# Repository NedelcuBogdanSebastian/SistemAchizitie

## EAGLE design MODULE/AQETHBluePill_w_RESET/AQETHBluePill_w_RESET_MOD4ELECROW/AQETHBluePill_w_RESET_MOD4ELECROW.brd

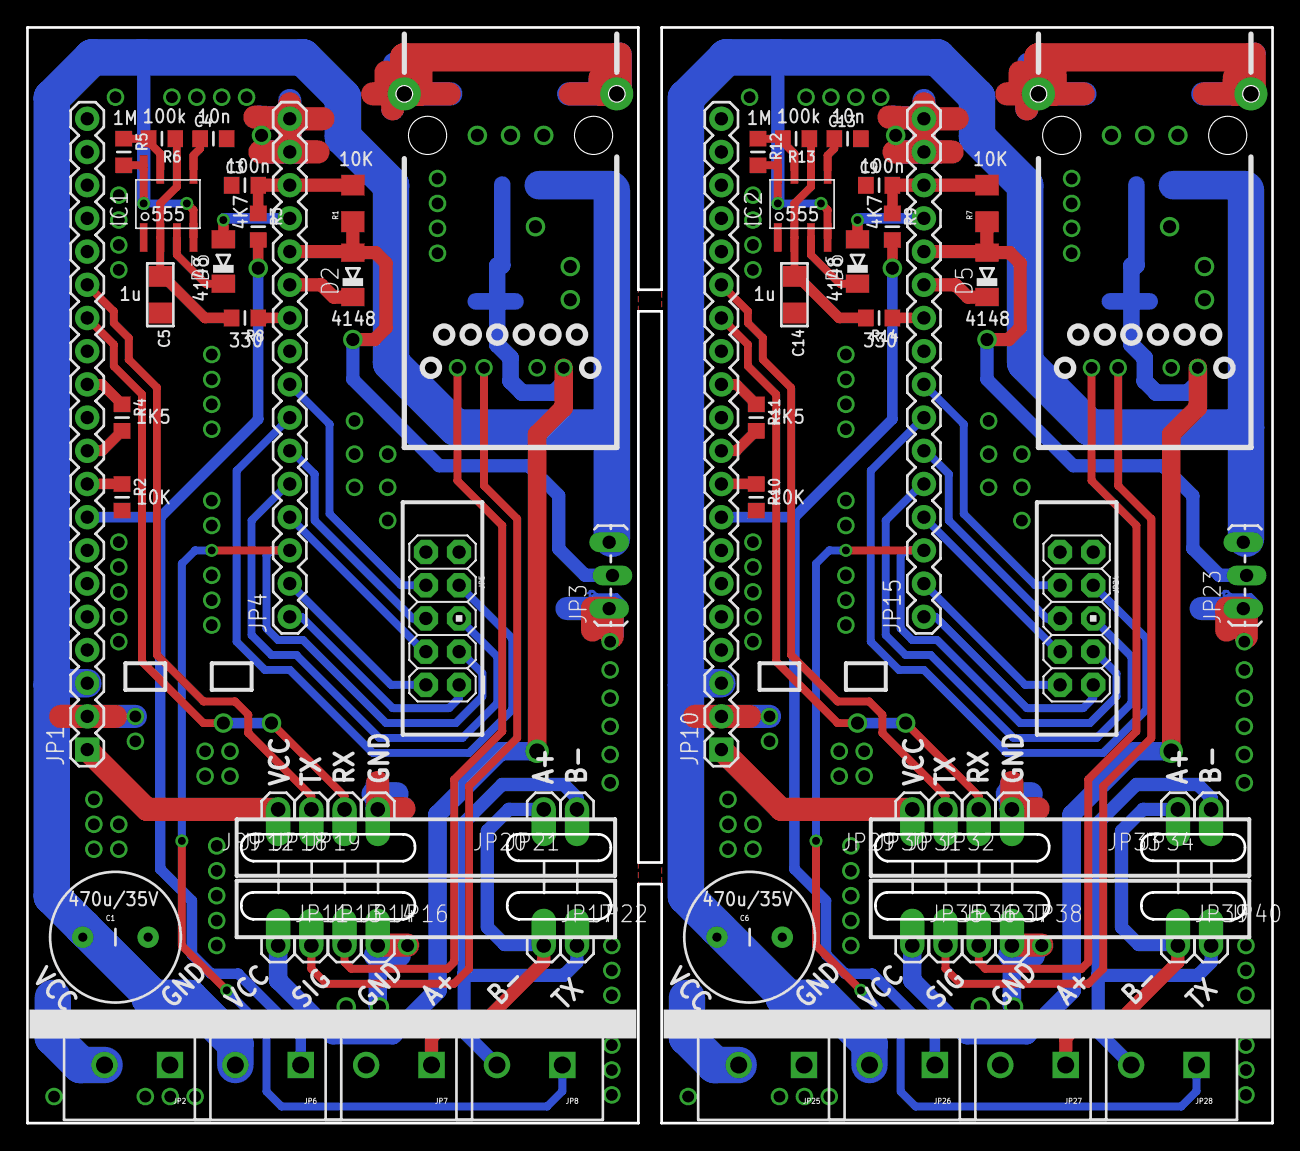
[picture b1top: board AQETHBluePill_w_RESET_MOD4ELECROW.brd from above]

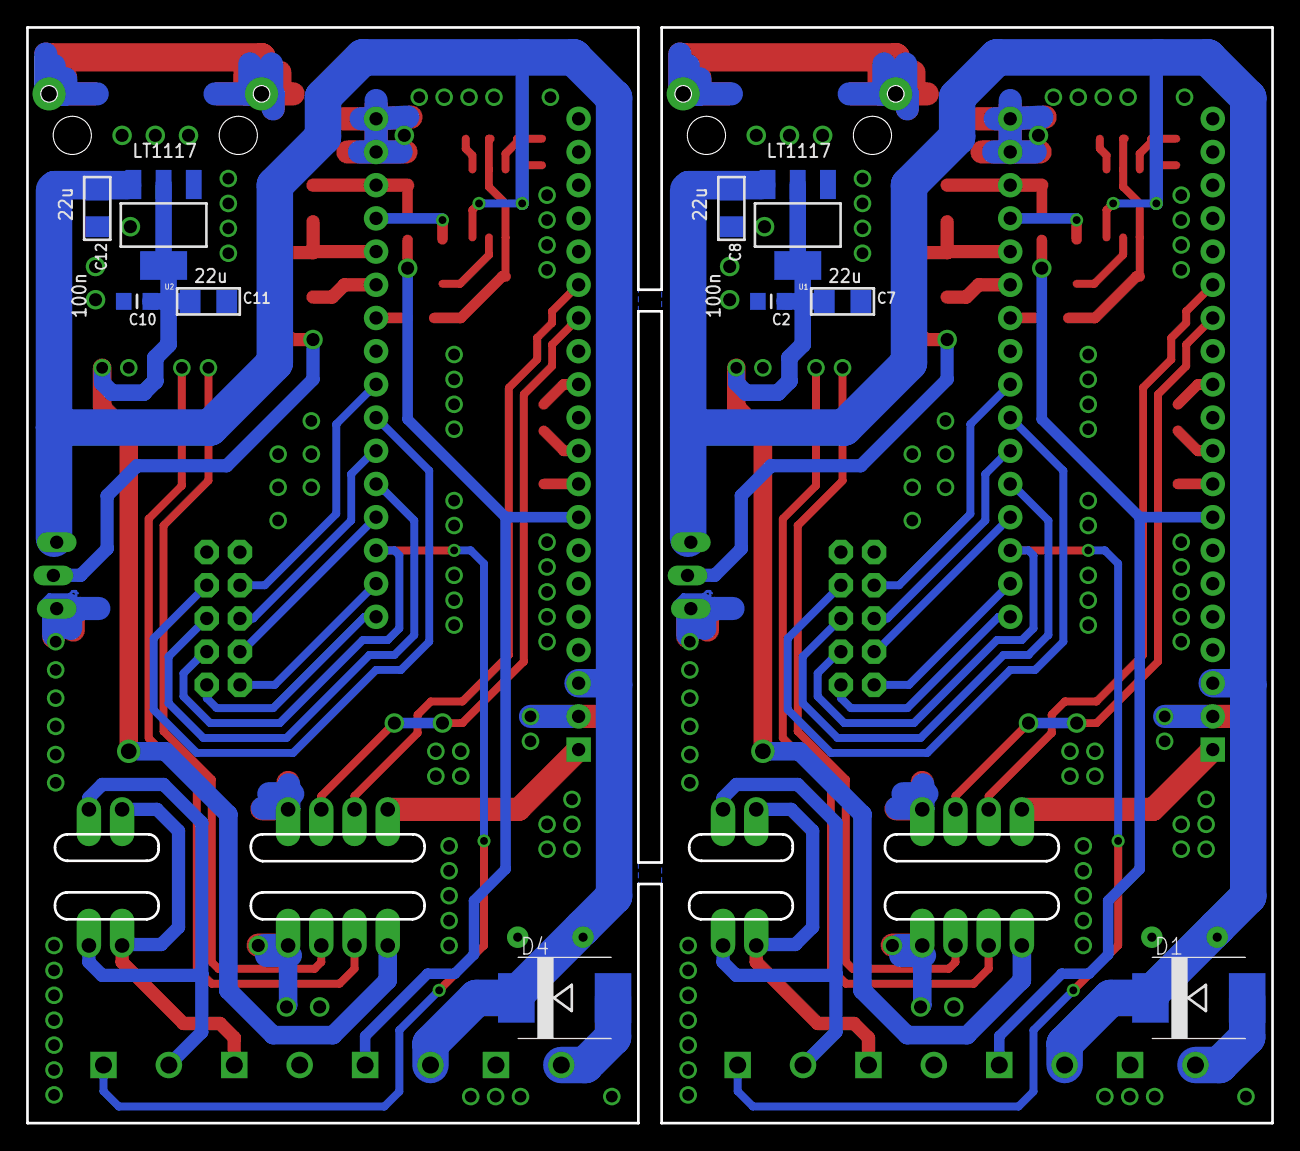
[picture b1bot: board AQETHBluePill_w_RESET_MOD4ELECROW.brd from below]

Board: 2 copper layers, 95.2 x 83.8 mm, 78 parts (10 on the bottom side), 60 nets.

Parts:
C1, C6: 470uF/35V; CAP-PTH-5MM
C2, C3, C9, C10: 100n; _0805MP
C4, C13: 10n; _0805MP
C5, C14: 1u; 1206
C7, C8, C11, C12: 22u; 1206
D1, D4: SS34; SMC
D2, D3, D5, D6: 1N4148; MINIMELF
IC1, IC2: IC_555-SOIC8; SOIC-8
JP1, JP10: M20; 1X20
JP2, JP6, JP7, JP8, JP25, JP26, JP27, JP28: SCREWTERMINAL-5MM-2
JP3, JP23: 1X03_LOCK_LONGPADS
JP4, JP15: M16PTH; 1X16
JP5, JP24: M05X2PTH; AVR_ICSP
JP9, JP11, JP12, JP13, JP14, JP16, JP17, JP18, JP19, JP20, JP21, JP22, JP29, JP30, JP31, JP32, JP33, JP34, JP35, JP36, JP37, JP38, JP39, JP40: M01OFFSET; 1X01_OFFSET
R1, R7: 10K; 1206
R2, R10: 10K; _0805MP
R3, R9: 4k7; _0805MP
R4, R11: 1K5; _0805MP
R5, R12: 1M; _0805MP
R6, R13: 100K; _0805MP
R8, R14: 330; _0805MP
U1, U2: SOT223

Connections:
3.3V: C3.2, JP4.14, R1.2, R3.1
3.3V1: C9.2, JP15.14, R7.2, R9.1
3V3_SECOND: JP1.1, JP9.1
3V3_SECOND1: JP10.1, JP29.1
5V: C1.1, C8.1, D1.C, IC1.4, IC1.8, JP1.3, JP3.3, JP6.2, R5.2, U1.3
5V1: C6.1, C12.1, D4.C, IC2.4, IC2.8, JP10.3, JP23.3, JP26.2, R12.2, U2.3
+A_1: JP27.1, JP33.1, JP39.1
+A_485: JP7.1, JP17.1, JP20.1
-B_1: JP28.2, JP34.1, JP40.1
-B_485: JP8.2, JP21.1, JP22.1
CTRL: C4.1, IC1.5
CTRL1: C13.1, IC2.5
DS18S20_SIGNAL_PIN: JP1.8, JP6.1, R3.2
DS18S20_SIGNAL_PIN1: JP10.8, JP26.1, R9.2
GND: C1.2, C2.2, C3.1, C4.2, C5.2, C7.2, C8.2, IC1.1, JP1.2, JP2.1, JP3.1, JP4.15, JP4.16, JP5.9, JP5.10, JP7.2, JP16.1, JP19.1, R2.2, U1.1
GND2: C6.2, C9.1, C10.2, C11.2, C12.2, C13.2, C14.2, IC2.1, JP10.2, JP15.15, JP15.16, JP23.1, JP24.9, JP24.10, JP25.1, JP27.2, JP32.1, JP38.1, R10.2, U2.1
HEARTBEAT: JP4.10, R8.1
HEARTBEAT1: JP15.10, R14.1
K1: JP4.1, JP5.1
K2: JP4.2, JP5.2
K3: JP15.1, JP24.1
K3_OR_TX1: JP15.3, JP24.3, JP28.1
K3_OR_TX2: JP4.3, JP5.3, JP8.1
K4: JP4.4, JP5.4
K5: JP4.5, JP5.5
K6: JP4.6, JP5.6
K7: JP4.7, JP5.7
K8: JP4.8, JP5.8
K9: JP15.2, JP24.2
K10: JP15.4, JP24.4
K11: JP15.5, JP24.5
K12: JP15.6, JP24.6
K13: JP15.7, JP24.7
K14: JP15.8, JP24.8
unnamed: JP1.10, R4.2
unnamed: JP1.9, R2.1
unnamed: JP1.12, R4.1
unnamed: JP10.9, R10.1
unnamed: D4.A, JP25.2
unnamed: C5.1, IC1.2, IC1.6, R6.1, R8.2
unnamed: D3.C, IC1.3
unnamed: IC1.7, R5.1, R6.2
unnamed: JP10.10, R11.2
unnamed: JP10.12, R11.1
unnamed: C14.1, IC2.2, IC2.6, R13.1, R14.2
unnamed: D1.A, JP2.2
unnamed: D6.C, IC2.3
unnamed: IC2.7, R12.1, R13.2
PB10_TX1: D5.C, JP15.11
PB10_TX3: D2.C, JP4.11
PB11_RX1: D5.A, JP15.12, JP23.2, R7.1
PB11_RX3: D2.A, JP3.2, JP4.12, R1.1
RESET: D3.A, JP4.13
RESET1: D6.A, JP15.13
RX1: JP1.14, JP18.1
RX2: JP10.14, JP31.1
TX1: JP1.15, JP12.1
TX2: JP10.15, JP30.1
VCC: C2.1, C7.1, JP11.1, U1.2, U1.4
VCC1: C10.1, C11.1, JP35.1, U2.2, U2.4

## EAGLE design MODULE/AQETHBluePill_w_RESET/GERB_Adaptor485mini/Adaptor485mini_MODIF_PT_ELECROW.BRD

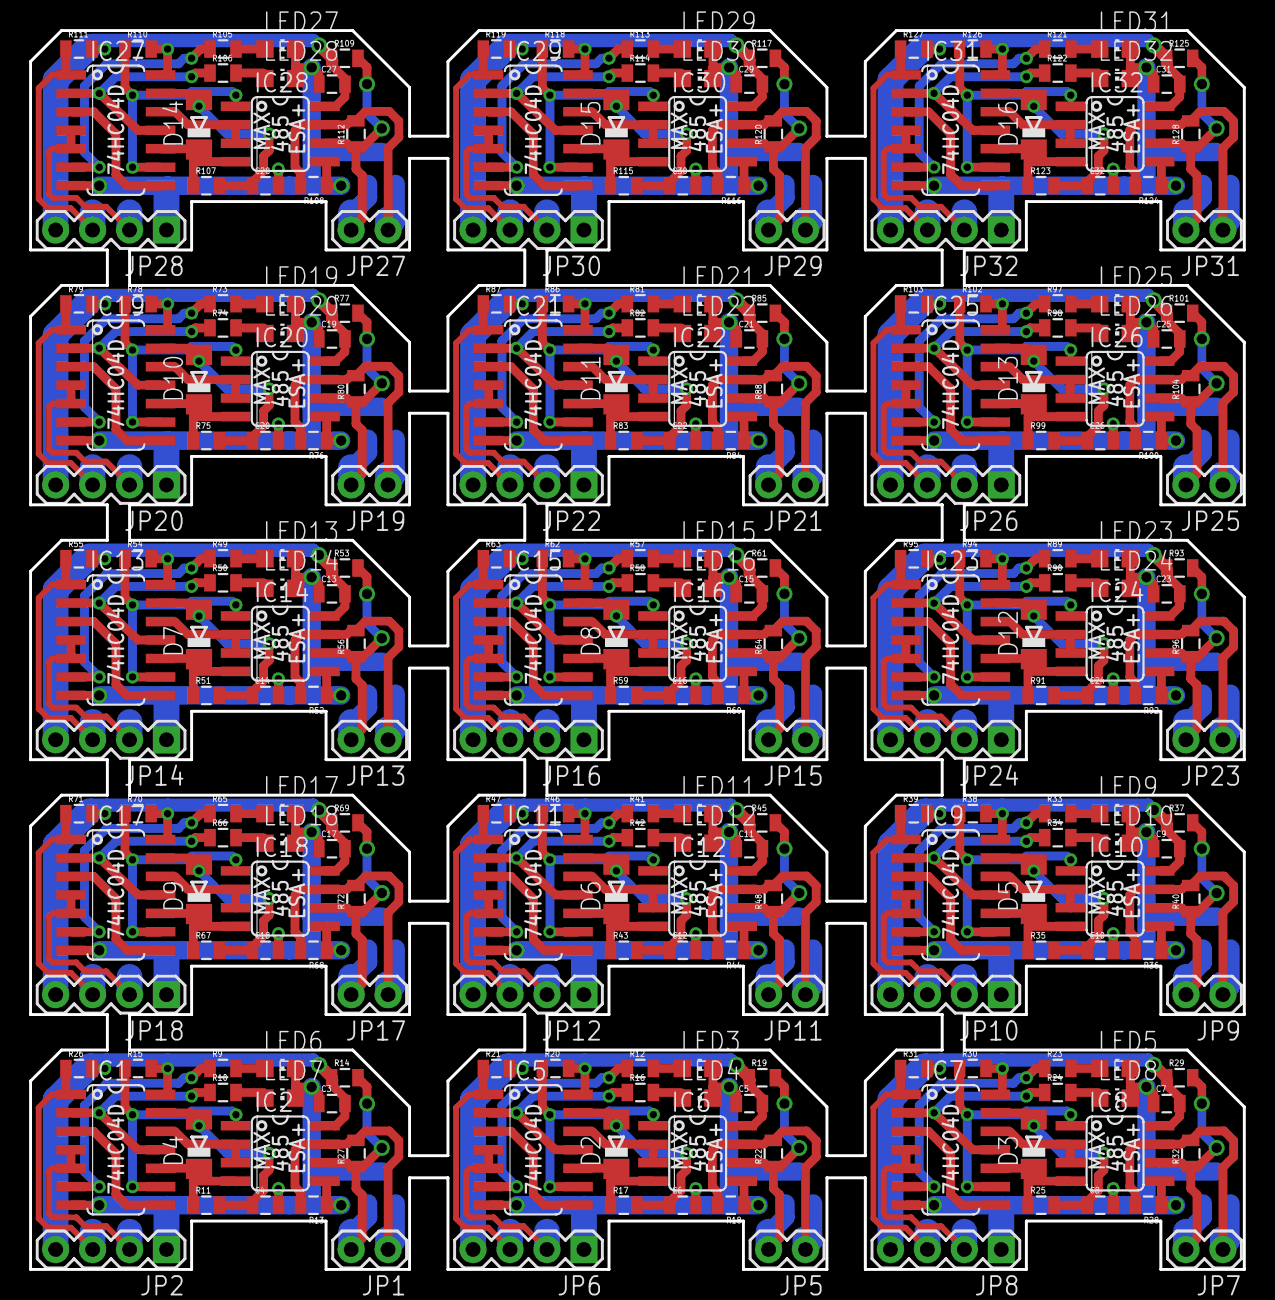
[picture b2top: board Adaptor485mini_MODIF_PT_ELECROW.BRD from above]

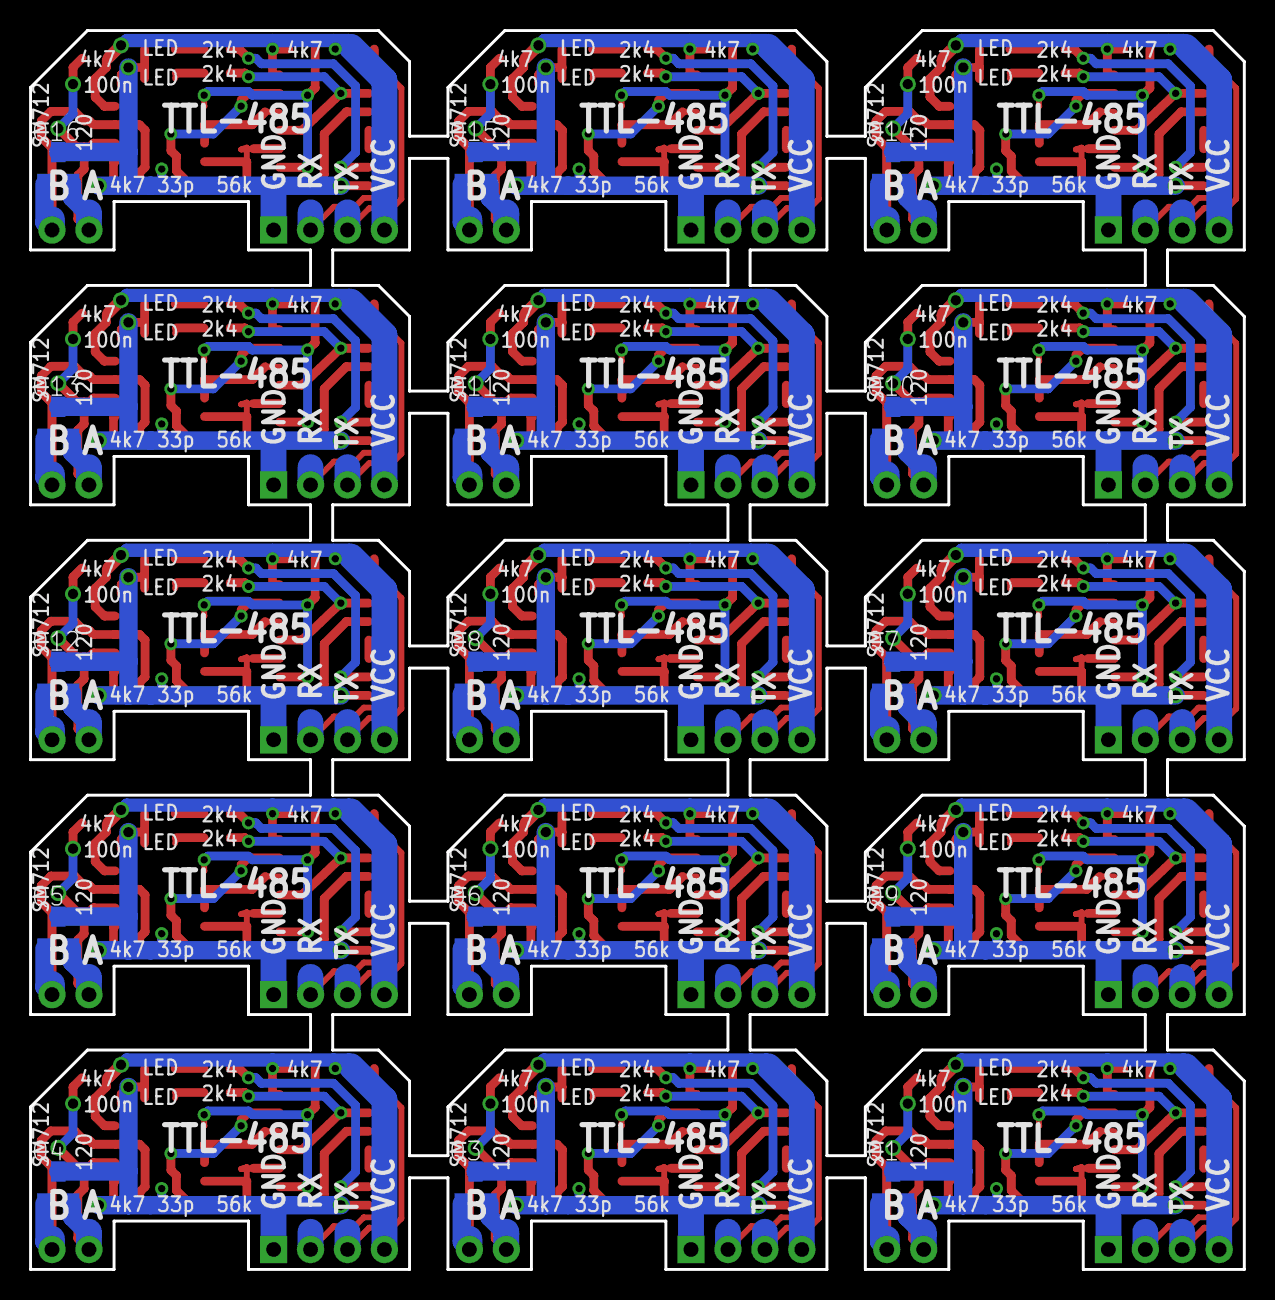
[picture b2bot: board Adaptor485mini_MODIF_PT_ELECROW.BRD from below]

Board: 2 copper layers, 83.5 x 85.2 mm, 270 parts (15 on the bottom side), 225 nets.

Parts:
C3, C5, C7, C9, C11, C13, C15, C17, C19, C21, C23, C25, C27, C29, C31: 100n; 0805
C4, C6, C8, C10, C12, C14, C16, C18, C20, C22, C24, C26, C28, C30, C32: 33pF; 0805
D2, D3, D4, D5, D6, D7, D8, D9, D10, D11, D12, D13, D14, D15, D16: 1N4148; MINIMELF
IC1, IC5, IC7, IC9, IC11, IC13, IC15, IC17, IC19, IC21, IC23, IC25, IC27, IC29, IC31: 74HC04D; SO14
IC2, IC6, IC8, IC10, IC12, IC14, IC16, IC18, IC20, IC22, IC24, IC26, IC28, IC30, IC32: MAX3468CSA; SO08
JP1, JP5, JP7, JP9, JP11, JP13, JP15, JP17, JP19, JP21, JP23, JP25, JP27, JP29, JP31: 1X02
JP2, JP6, JP8, JP10, JP12, JP14, JP16, JP18, JP20, JP22, JP24, JP26, JP28, JP30, JP32: 1X04
LED3, LED4, LED5, LED6, LED7, LED8, LED9, LED10, LED11, LED12, LED13, LED14, LED15, LED16, LED17, LED18, LED19, LED20, LED21, LED22, LED23, LED24, LED25, LED26, LED27, LED28, LED29, LED30, LED31, LED32: CHIP-LED0805
Q1, Q3, Q4, Q5, Q6, Q7, Q8, Q9, Q10, Q11, Q12, Q13, Q14, Q15, Q16: BCX70SMD; SOT23
R9, R10, R12, R16, R23, R24, R33, R34, R41, R42, R49, R50, R57, R58, R65, R66, R73, R74, R81, R82, R89, R90, R97, R98, R105, R106, R113, R114, R121, R122: 2K4; 0805
R11, R17, R25, R35, R43, R51, R59, R67, R75, R83, R91, R99, R107, R115, R123: 56K; 0805
R13, R14, R15, R18, R19, R20, R21, R26, R28, R29, R30, R31, R36, R37, R38, R39, R44, R45, R46, R47, R52, R53, R54, R55, R60, R61, R62, R63, R68, R69, R70, R71, R76, R77, R78, R79, R84, R85, R86, R87, R92, R93, R94, R95, R100, R101, R102, R103, R108, R109, R110, R111, R116, R117, R118, R119, R124, R125, R126, R127: 4K7; 0805
R22, R27, R32, R40, R48, R56, R64, R72, R80, R88, R96, R104, R112, R120, R128: 120; 0805

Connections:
3.3V: C3.2, IC1.14, IC2.8, JP2.4, R14.1, R15.2, R26.2
3.3V2: C5.2, IC5.14, IC6.8, JP6.4, R19.1, R20.2, R21.2
3.3V3: C7.2, IC7.14, IC8.8, JP8.4, R29.1, R30.2, R31.2
3.3V4: C9.2, IC9.14, IC10.8, JP10.4, R37.1, R38.2, R39.2
3.3V5: C11.2, IC11.14, IC12.8, JP12.4, R45.1, R46.2, R47.2
3.3V6: C13.2, IC13.14, IC14.8, JP14.4, R53.1, R54.2, R55.2
3.3V7: C15.2, IC15.14, IC16.8, JP16.4, R61.1, R62.2, R63.2
3.3V8: C17.2, IC17.14, IC18.8, JP18.4, R69.1, R70.2, R71.2
3.3V9: C19.2, IC19.14, IC20.8, JP20.4, R77.1, R78.2, R79.2
3.3V10: C21.2, IC21.14, IC22.8, JP22.4, R85.1, R86.2, R87.2
3.3V11: C23.2, IC23.14, IC24.8, JP24.4, R93.1, R94.2, R95.2
3.3V12: C25.2, IC25.14, IC26.8, JP26.4, R101.1, R102.2, R103.2
3.3V13: C27.2, IC27.14, IC28.8, JP28.4, R109.1, R110.2, R111.2
3.3V14: C29.2, IC29.14, IC30.8, JP30.4, R117.1, R118.2, R119.2
3.3V15: C31.2, IC31.14, IC32.8, JP32.4, R125.1, R126.2, R127.2
A+: IC2.6, JP1.2, Q1.2, R14.2, R27.1
A+2: IC6.6, JP5.2, Q3.2, R19.2, R22.1
A+3: IC8.6, JP7.2, Q4.2, R29.2, R32.1
A+4: IC10.6, JP9.2, Q5.2, R37.2, R40.1
A+5: IC12.6, JP11.2, Q6.2, R45.2, R48.1
A+6: IC14.6, JP13.2, Q7.2, R53.2, R56.1
A+7: IC16.6, JP15.2, Q8.2, R61.2, R64.1
A+8: IC18.6, JP17.2, Q9.2, R69.2, R72.1
A+9: IC20.6, JP19.2, Q10.2, R77.2, R80.1
A+10: IC22.6, JP21.2, Q11.2, R85.2, R88.1
A+11: IC24.6, JP23.2, Q12.2, R93.2, R96.1
A+12: IC26.6, JP25.2, Q13.2, R101.2, R104.1
A+13: IC28.6, JP27.2, Q14.2, R109.2, R112.1
A+14: IC30.6, JP29.2, Q15.2, R117.2, R120.1
A+15: IC32.6, JP31.2, Q16.2, R125.2, R128.1
B-: IC2.7, JP1.1, Q1.1, R13.2, R27.2
B-2: IC6.7, JP5.1, Q3.1, R18.2, R22.2
B-3: IC8.7, JP7.1, Q4.1, R28.2, R32.2
B-4: IC10.7, JP9.1, Q5.1, R36.2, R40.2
B-5: IC12.7, JP11.1, Q6.1, R44.2, R48.2
B-6: IC14.7, JP13.1, Q7.1, R52.2, R56.2
B-7: IC16.7, JP15.1, Q8.1, R60.2, R64.2
B-8: IC18.7, JP17.1, Q9.1, R68.2, R72.2
B-9: IC20.7, JP19.1, Q10.1, R76.2, R80.2
B-10: IC22.7, JP21.1, Q11.1, R84.2, R88.2
B-11: IC24.7, JP23.1, Q12.1, R92.2, R96.2
B-12: IC26.7, JP25.1, Q13.1, R100.2, R104.2
B-13: IC28.7, JP27.1, Q14.1, R108.2, R112.2
B-14: IC30.7, JP29.1, Q15.1, R116.2, R120.2
B-15: IC32.7, JP31.1, Q16.1, R124.2, R128.2
GND: C3.1, C4.2, IC1.7, IC2.5, JP2.1, LED6.C, LED7.C, Q1.3, R13.1
GND3: C5.1, C6.2, IC5.7, IC6.5, JP6.1, LED3.C, LED4.C, Q3.3, R18.1
GND4: C7.1, C8.2, IC7.7, IC8.5, JP8.1, LED5.C, LED8.C, Q4.3, R28.1
GND5: C9.1, C10.2, IC9.7, IC10.5, JP10.1, LED9.C, LED10.C, Q5.3, R36.1
GND6: C11.1, C12.2, IC11.7, IC12.5, JP12.1, LED11.C, LED12.C, Q6.3, R44.1
GND7: C13.1, C14.2, IC13.7, IC14.5, JP14.1, LED13.C, LED14.C, Q7.3, R52.1
GND8: C15.1, C16.2, IC15.7, IC16.5, JP16.1, LED15.C, LED16.C, Q8.3, R60.1
GND9: C17.1, C18.2, IC17.7, IC18.5, JP18.1, LED17.C, LED18.C, Q9.3, R68.1
GND10: C19.1, C20.2, IC19.7, IC20.5, JP20.1, LED19.C, LED20.C, Q10.3, R76.1
GND11: C21.1, C22.2, IC21.7, IC22.5, JP22.1, LED21.C, LED22.C, Q11.3, R84.1
GND12: C23.1, C24.2, IC23.7, IC24.5, JP24.1, LED23.C, LED24.C, Q12.3, R92.1
GND13: C25.1, C26.2, IC25.7, IC26.5, JP26.1, LED25.C, LED26.C, Q13.3, R100.1
GND14: C27.1, C28.2, IC27.7, IC28.5, JP28.1, LED27.C, LED28.C, Q14.3, R108.1
GND15: C29.1, C30.2, IC29.7, IC30.5, JP30.1, LED29.C, LED30.C, Q15.3, R116.1
GND16: C31.1, C32.2, IC31.7, IC32.5, JP32.1, LED31.C, LED32.C, Q16.3, R124.1
unnamed: IC5.9, IC6.1, R20.1
unnamed: IC5.3, IC5.8
unnamed: C6.1, D2.A, IC5.13, R17.2
unnamed: IC5.6, R12.1
unnamed: D2.C, IC5.10, IC6.4, R17.1
unnamed: IC5.12, IC6.2, IC6.3
unnamed: LED7.A, R10.2
unnamed: LED6.A, R9.2
unnamed: LED4.A, R16.2
unnamed: IC1.2, IC1.11, R10.1
unnamed: LED3.A, R12.2
unnamed: IC1.9, IC2.1, R15.1
unnamed: IC5.2, IC5.11, R16.1
unnamed: IC1.3, IC1.8
unnamed: C4.1, D4.A, IC1.13, R11.2
unnamed: IC7.9, IC8.1, R30.1
unnamed: IC7.3, IC7.8
unnamed: IC1.6, R9.1
unnamed: C8.1, D3.A, IC7.13, R25.2
unnamed: D4.C, IC1.10, IC2.4, R11.1
unnamed: IC1.12, IC2.2, IC2.3
unnamed: IC7.6, R23.1
unnamed: D3.C, IC7.10, IC8.4, R25.1
unnamed: IC7.12, IC8.2, IC8.3
unnamed: LED8.A, R24.2
unnamed: LED5.A, R23.2
unnamed: IC7.2, IC7.11, R24.1
unnamed: IC9.9, IC10.1, R38.1
unnamed: IC9.3, IC9.8
unnamed: C10.1, D5.A, IC9.13, R35.2
unnamed: IC9.6, R33.1
unnamed: D5.C, IC9.10, IC10.4, R35.1
unnamed: IC9.12, IC10.2, IC10.3
unnamed: LED10.A, R34.2
unnamed: LED9.A, R33.2
unnamed: IC9.2, IC9.11, R34.1
unnamed: IC11.9, IC12.1, R46.1
unnamed: IC11.3, IC11.8
unnamed: C12.1, D6.A, IC11.13, R43.2
unnamed: IC11.6, R41.1
unnamed: D6.C, IC11.10, IC12.4, R43.1
unnamed: IC11.12, IC12.2, IC12.3
unnamed: LED12.A, R42.2
unnamed: LED11.A, R41.2
unnamed: IC11.2, IC11.11, R42.1
unnamed: IC13.9, IC14.1, R54.1
unnamed: IC13.3, IC13.8
unnamed: C14.1, D7.A, IC13.13, R51.2
unnamed: IC13.6, R49.1
unnamed: D7.C, IC13.10, IC14.4, R51.1
unnamed: IC13.12, IC14.2, IC14.3
unnamed: LED14.A, R50.2
unnamed: LED13.A, R49.2
unnamed: IC13.2, IC13.11, R50.1
unnamed: IC15.9, IC16.1, R62.1
unnamed: IC15.3, IC15.8
unnamed: C16.1, D8.A, IC15.13, R59.2
unnamed: IC15.6, R57.1
unnamed: D8.C, IC15.10, IC16.4, R59.1
unnamed: IC15.12, IC16.2, IC16.3
unnamed: LED16.A, R58.2
unnamed: LED15.A, R57.2
unnamed: IC15.2, IC15.11, R58.1
unnamed: IC17.9, IC18.1, R70.1
unnamed: IC17.3, IC17.8
unnamed: C18.1, D9.A, IC17.13, R67.2
unnamed: IC17.6, R65.1
unnamed: D9.C, IC17.10, IC18.4, R67.1
unnamed: IC17.12, IC18.2, IC18.3
unnamed: LED18.A, R66.2
unnamed: LED17.A, R65.2
unnamed: IC17.2, IC17.11, R66.1
unnamed: IC19.9, IC20.1, R78.1
unnamed: IC19.3, IC19.8
unnamed: C20.1, D10.A, IC19.13, R75.2
unnamed: IC19.6, R73.1
unnamed: D10.C, IC19.10, IC20.4, R75.1
unnamed: IC19.12, IC20.2, IC20.3
unnamed: LED20.A, R74.2
unnamed: LED19.A, R73.2
unnamed: IC19.2, IC19.11, R74.1
unnamed: IC21.9, IC22.1, R86.1
unnamed: IC21.3, IC21.8
unnamed: C22.1, D11.A, IC21.13, R83.2
unnamed: IC21.6, R81.1
unnamed: D11.C, IC21.10, IC22.4, R83.1
unnamed: IC21.12, IC22.2, IC22.3
unnamed: LED22.A, R82.2
unnamed: LED21.A, R81.2
unnamed: IC21.2, IC21.11, R82.1
unnamed: IC23.9, IC24.1, R94.1
unnamed: IC23.3, IC23.8
unnamed: C24.1, D12.A, IC23.13, R91.2
unnamed: IC23.6, R89.1
unnamed: D12.C, IC23.10, IC24.4, R91.1
unnamed: IC23.12, IC24.2, IC24.3
unnamed: LED24.A, R90.2
unnamed: LED23.A, R89.2
unnamed: IC23.2, IC23.11, R90.1
unnamed: IC25.9, IC26.1, R102.1
unnamed: IC25.3, IC25.8
unnamed: C26.1, D13.A, IC25.13, R99.2
unnamed: IC25.6, R97.1
unnamed: D13.C, IC25.10, IC26.4, R99.1
unnamed: IC25.12, IC26.2, IC26.3
unnamed: LED26.A, R98.2
unnamed: LED25.A, R97.2
unnamed: IC25.2, IC25.11, R98.1
unnamed: IC27.9, IC28.1, R110.1
unnamed: IC27.3, IC27.8
unnamed: C28.1, D14.A, IC27.13, R107.2
unnamed: IC27.6, R105.1
unnamed: D14.C, IC27.10, IC28.4, R107.1
unnamed: IC27.12, IC28.2, IC28.3
unnamed: LED28.A, R106.2
unnamed: LED27.A, R105.2
unnamed: IC27.2, IC27.11, R106.1
unnamed: IC29.9, IC30.1, R118.1
unnamed: IC29.3, IC29.8
unnamed: C30.1, D15.A, IC29.13, R115.2
unnamed: IC29.6, R113.1
unnamed: D15.C, IC29.10, IC30.4, R115.1
unnamed: IC29.12, IC30.2, IC30.3
unnamed: LED30.A, R114.2
unnamed: LED29.A, R113.2
unnamed: IC29.2, IC29.11, R114.1
unnamed: IC31.9, IC32.1, R126.1
unnamed: IC31.3, IC31.8
unnamed: C32.1, D16.A, IC31.13, R123.2
unnamed: IC31.6, R121.1
unnamed: D16.C, IC31.10, IC32.4, R123.1
unnamed: IC31.12, IC32.2, IC32.3
unnamed: LED32.A, R122.2
unnamed: LED31.A, R121.2
unnamed: IC31.2, IC31.11, R122.1
RX: IC1.1, JP2.3, R26.1
RX2: IC5.1, JP6.3, R21.1
RX3: IC7.1, JP8.3, R31.1
RX4: IC9.1, JP10.3, R39.1
RX5: IC11.1, JP12.3, R47.1
RX6: IC13.1, JP14.3, R55.1
RX7: IC15.1, JP16.3, R63.1
RX8: IC17.1, JP18.3, R71.1
RX9: IC19.1, JP20.3, R79.1
RX10: IC21.1, JP22.3, R87.1
RX11: IC23.1, JP24.3, R95.1
RX12: IC25.1, JP26.3, R103.1
RX13: IC27.1, JP28.3, R111.1
RX14: IC29.1, JP30.3, R119.1
RX15: IC31.1, JP32.3, R127.1
TX: IC1.4, IC1.5, JP2.2
TX2: IC5.4, IC5.5, JP6.2
TX3: IC7.4, IC7.5, JP8.2
TX4: IC9.4, IC9.5, JP10.2
TX5: IC11.4, IC11.5, JP12.2
TX6: IC13.4, IC13.5, JP14.2
TX7: IC15.4, IC15.5, JP16.2
TX8: IC17.4, IC17.5, JP18.2
TX9: IC19.4, IC19.5, JP20.2
TX10: IC21.4, IC21.5, JP22.2
TX11: IC23.4, IC23.5, JP24.2
TX12: IC25.4, IC25.5, JP26.2
TX13: IC27.4, IC27.5, JP28.2
TX14: IC29.4, IC29.5, JP30.2
TX15: IC31.4, IC31.5, JP32.2

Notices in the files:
parts and their libraries:
SparkFun-Connectors: Licensing: CC v3.0 Share-Alike You are welcome to use this library for commercial purposes.
SparkFun-Passives: Licensing: Creative Commons ShareAlike 4.0 International - https://creativecommons.org/licenses/by-sa/4.0
